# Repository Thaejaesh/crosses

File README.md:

# FORKED FROM ORIGINAL CREATOR: Good-Great-Grand-Wonderful @ https://github.com/Good-Great-Grand-Wonderful/crosses
# Crosses

A modular ergonomic columar staggered keyboard by Good Great Grand Wonderful LLC. 

Made with a precise trackball sensor. Eliminating the need to have another pointing device, everything is within reach.

Available at http://ergokeyboards.com

### Features

- Matrix with a thumb cluster that works better with our opposable thumbs!
- Main matrix layouts of: 3x5, 3x6, and 4x6
- Kailh Choc hotswap sockets, so you can explore and find your perfect switch
- Left/Right or dualing trackballs
- Optional OLED screens

### Firmware

QMK: https://github.com/Good-Great-Grand-Wonderful/qmk_firmware/tree/gggw/crosses

Vial: https://github.com/Good-Great-Grand-Wonderful/crosses-vial-qmk/tree/gggw/crosses

ZMK(testing): https://github.com/Good-Great-Grand-Wonderful/crosses-zmk

### Gerbers

Production ready and prepped with JLCPCB part numbers: [Gerbers](Gerbers)

### BOM

#### Cases

N = Number of trackballs

| Qty       |3x5 | 3x6 | 4x6 | Item                                              | Notes                             |
|-----------|----|-----|-----|---------------------------------------------------|-----------------------------------|
| 24        | x  | x   | x   | 3mm Heat set inserts                              |                                   |
| 16        | x  | x   | x   | 3mm x 5mm Hex Bolts                               | +2 for every trackball you delete |
| 2xN       | x  | x   | x   | 3mm x 12mm Hex Bolts                              |                                   |
| 2xN       | x  | x   | x   | 3mm x 8mm Hex Bolts                               |                                   |
| 1         | x  | x   | x   | Thumb Cluster PCB Panel                           |                                   |
| 4         | x  | x   | x   | Hirose FH12-14S 0.5SH 1x14 1MP P0.50mm Horizontal |                                   |
| 2         | x  | x   | x   | SM06B-SRSS-TB(LF)(SN)                             |                                   |
| 1         | x  |     |     | 3x5 Matrix PCB Panel                              |                                   |
| 1         |    | x   |     | 3x6 Matrix PCB Panel                              |                                   |
| 1         |    |     | x   | 4x6 Matrix PCB Panel                              |                                   |
| 2         | x  |     |     | 100mm 14p 0.5mm pitch FFC cables                  |                                   |
| 2         |    | x   | x   | 150mm 14p 0.5mm pitch FFC cables                  |                                   |
| 1xN       | x  | x   | x   | 100mm 6p JST SH 1.0 Same direction cables         |                                   |
| 2x        | x  | x   | x   | Thumb Cluster Case (one should be flipped)        |                                   |
| 2x        | x  |     |     | 3x5 Matrix Case    (one should be flipped)        |                                   |
| 2x        |    | x   |     | 3x6 Matrix Case    (one should be flipped)        |                                   |
| 2x        |    |     | x   | 4x6 Matrix Case    (one should be flipped)        |                                   |
| 36x       | x  |     |     | Kailh Choc Hotswap Sockets                        |                                   |
| 42x       |    | x   |     | Kailh Choc Hotswap Sockets                        |                                   |
| 54x       |    |     | x   | Kailh Choc Hotswap Sockets                        |                                   |
| 36x       | x  |     |     | 1N4148 SMD SOD-123 Resistors                      |                                   |
| 42x       |    | x   |     | 1N4148 SMD SOD-123 Resistors                      |                                   |
| 54x       |    |     | x   | 1N4148 SMD SOD-123 Resistors                      |                                   |
| 1xN       | x  | x   | x   | Trackball Mount    (one should be flipped)        |                                   |
| 1xN       | x  | x   | x   | Trackball PCB                                     | [Repo](https://github.com/Good-Great-Grand-Wonderful/PMW3360DM-T2QU)                                  |
| 1xN       | x  | x   | x   | PMW3360DM-T2QU + LM19-LSI                         | or sub a PMW3389                  |
| 1xN       | x  | x   | x   | Trackball Carrier Base                            |                                   |
| 1xN       | x  | x   | x   | Trackball Carrier Top                             |                                   |

## License

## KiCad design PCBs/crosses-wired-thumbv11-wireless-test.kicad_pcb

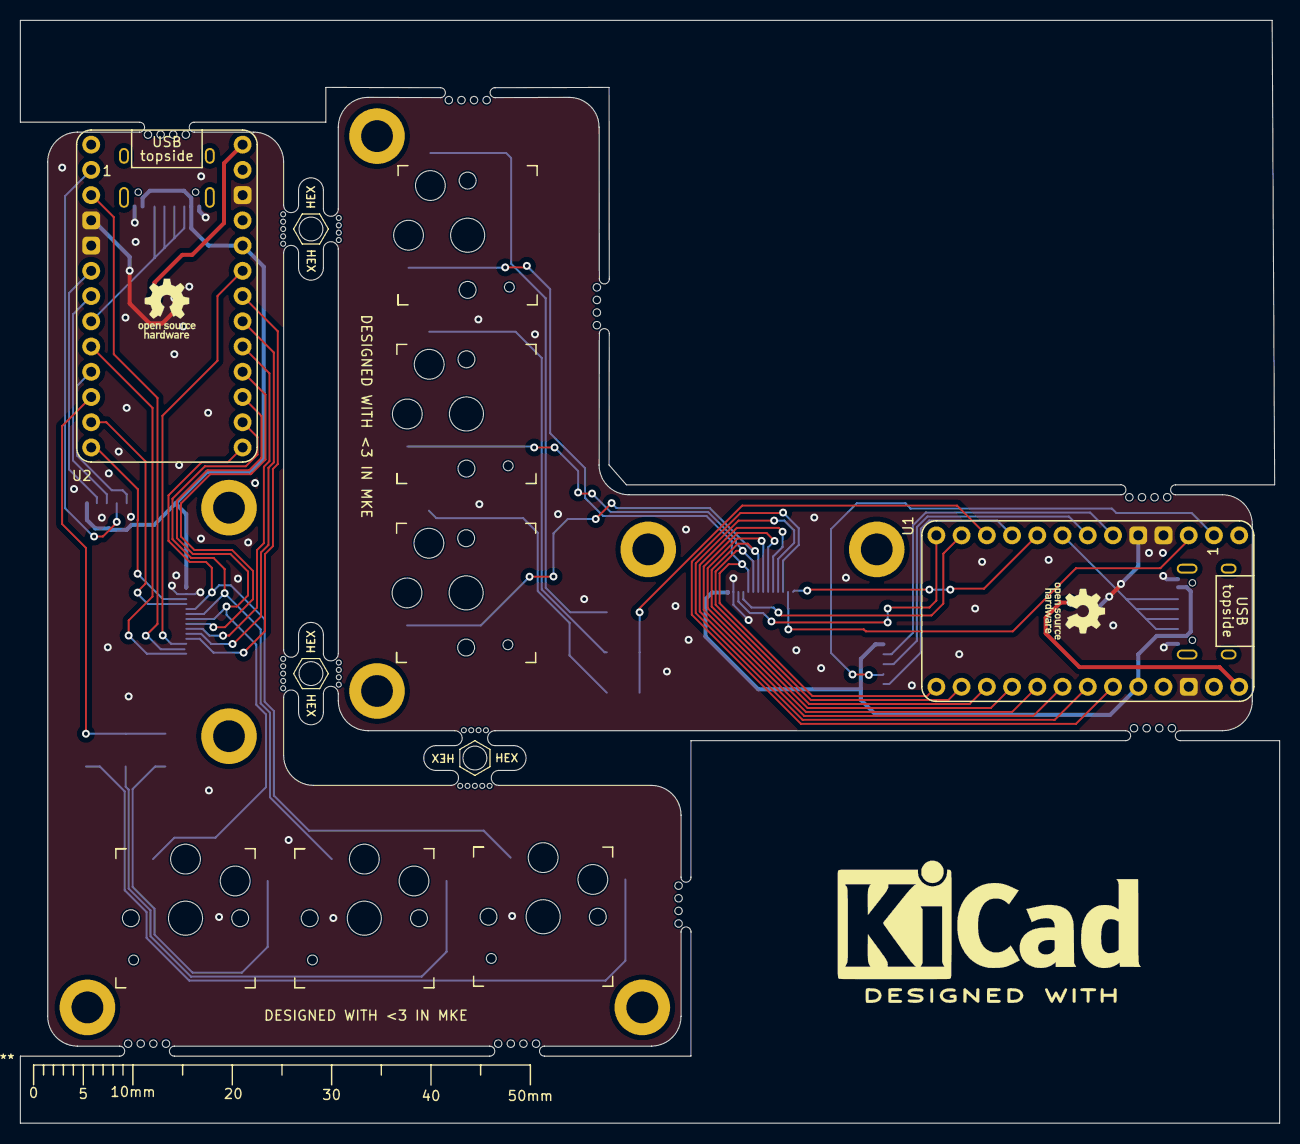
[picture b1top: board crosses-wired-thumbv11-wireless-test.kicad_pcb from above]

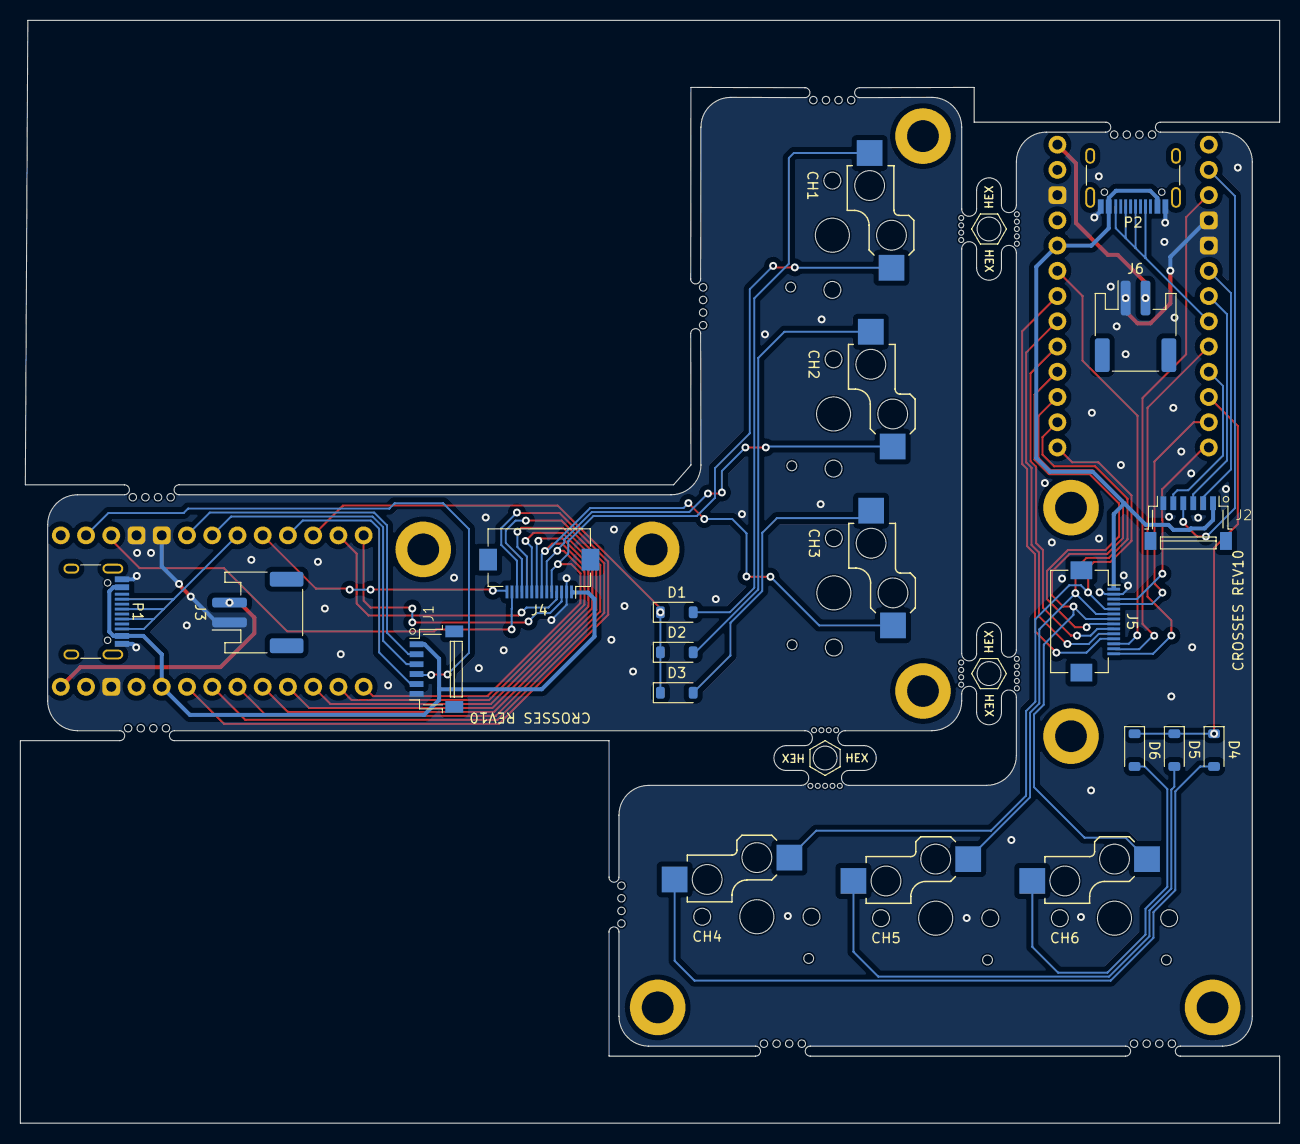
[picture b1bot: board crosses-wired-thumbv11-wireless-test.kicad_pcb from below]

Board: 2 copper layers, 126.8 x 111.0 mm, 33 parts (18 on the bottom side), 47 nets.

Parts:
CH1, CH2, CH3, CH4, CH5, CH6: CPG135001S30; Kailh_socket_PG1350
D1, D2, D3, D4, D5, D6: 1N4148; D_SOD-123
H1, H1#2, H2, H2#2, H3, H3#2, H3#3, H3#4: MountingHole; MountingHole_3.2mm_M3_DIN965_Pad
J1, J2: SM06B-SRSS-TB(LF)(SN)
J3, J6: Conn_01x02_Socket; JST_PH_S2B-PH-SM4-TB_1x02-1MP_P2.00mm_Horizontal
J4, J5: Conn_01x14_Pin; Hirose_FH12-14S-0.5SH_1x14-1MP_P0.50mm_Horizontal
MB5, MB5#2, MB5#3: 5.5mm; mousebites_5p5mm_easysnap
P1, P2: TYPE-C-31-M-12 USB; USB_C_Receptacle_HRO_TYPE-C-31-M-12
U1, U2: supermini nrf / nice nano v2; Helios_AH_USBup

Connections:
GND: J1.6, J2.6, J3.1, J4.2, J5.2, J6.1, P1.A1 (GND), P1.A12 (GND), P1.B1 (GND), P1.B12 (GND), P2.A1 (GND), P2.A12 (GND), P2.B1 (GND), P2.B12 (GND), U1.3 (GND), U1.4 (GND), U1.14 (GND), U2.3 (GND), U2.4 (GND), U2.14 (GND)
L-COL0: J4.9, U1.20 (F7)
L-COL1: J4.8, U1.21 (B1)
L-COL2: CH1.1, J4.5, U1.24 (B6)
L-COL3: CH2.1, J4.6, U1.23 (B2)
L-COL4: CH3.1, J4.7, U1.22 (B3)
L-COLP: J4.13, U1.2 (D2-RX)
L-CS: J1.5, U1.9 (D7)
L-DATA: P1.A5 (CC1), P1.A6 (D+), P1.B5 (CC2), P1.B6 (D+), U1.7 (D4)
L-I2C SCL: J4.3, U1.12 (B5)
L-I2C SDA: J4.4, U1.11 (B4)
L-MISO: J1.4, U1.1 (D3-TX)
L-MOSI: J1.3, U1.6 (D0)
L-ROW0: J4.10, U1.19 (F6)
L-ROW1: J4.11, U1.18 (F5)
L-ROW2: J4.12, U1.17 (F4)
L-ROW3: D1.1 (K), D2.1 (K), D3.1 (K), U1.10 (E6)
L-ROWH: J4.14, U1.8 (C6)
L-SCK: J1.2, U1.5 (D1)
L-VCC: J1.1, J4.1, P1.A4 (VBUS), P1.A9 (VBUS), P1.B4 (VBUS), P1.B9 (VBUS), U1.16 (VCC)
unnamed: CH1.2, D1.2 (A)
unnamed: CH2.2, D2.2 (A)
unnamed: CH3.2, D3.2 (A)
unnamed: CH4.2, D4.2 (A)
unnamed: CH5.2, D5.2 (A)
unnamed: CH6.2, D6.2 (A)
R-COL0: J5.9, U2.20 (F7)
R-COL1: J5.8, U2.21 (B1)
R-COL2: CH4.1, J5.5, U2.24 (B6)
R-COL3: CH5.1, J5.6, U2.23 (B2)
R-COL4: CH6.1, J5.7, U2.22 (B3)
R-COLP: J5.13, U2.2 (D2-RX)
R-CS: J2.5, U2.9 (D7)
R-DATA: P2.A5 (CC1), P2.A6 (D+), P2.B5 (CC2), P2.B6 (D+), U2.7 (D4)
R-I2C SCL: J5.3, U2.12 (B5)
R-I2C SDA: J5.4, U2.11 (B4)
R-MISO: J2.4, U2.1 (D3-TX)
R-MOSI: J2.3, U2.6 (D0)
R-ROW0: J5.10, U2.19 (F6)
R-ROW1: J5.11, U2.18 (F5)
R-ROW2: J5.12, U2.17 (F4)
R-ROW3: D4.1 (K), D5.1 (K), D6.1 (K), U2.10 (E6)
R-ROWH: J5.14, U2.8 (C6)
R-SCK: J2.2, U2.5 (D1)
R-VCC: J2.1, J5.1, P2.A4 (VBUS), P2.A9 (VBUS), P2.B4 (VBUS), P2.B9 (VBUS), U2.16 (VCC)
VBATTL: J3.2, U1.30 (VBUS)
VBATTR: J6.2, U2.30 (VBUS)

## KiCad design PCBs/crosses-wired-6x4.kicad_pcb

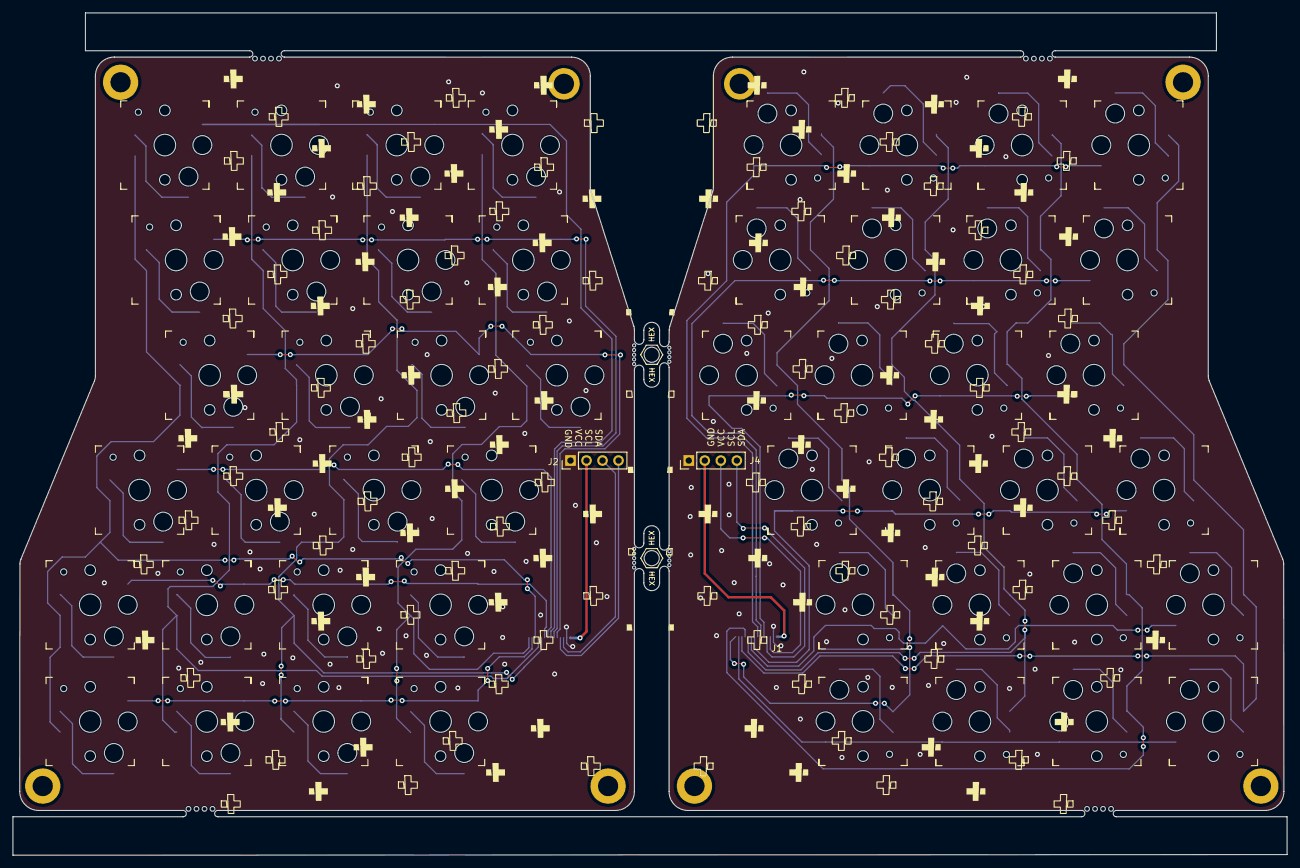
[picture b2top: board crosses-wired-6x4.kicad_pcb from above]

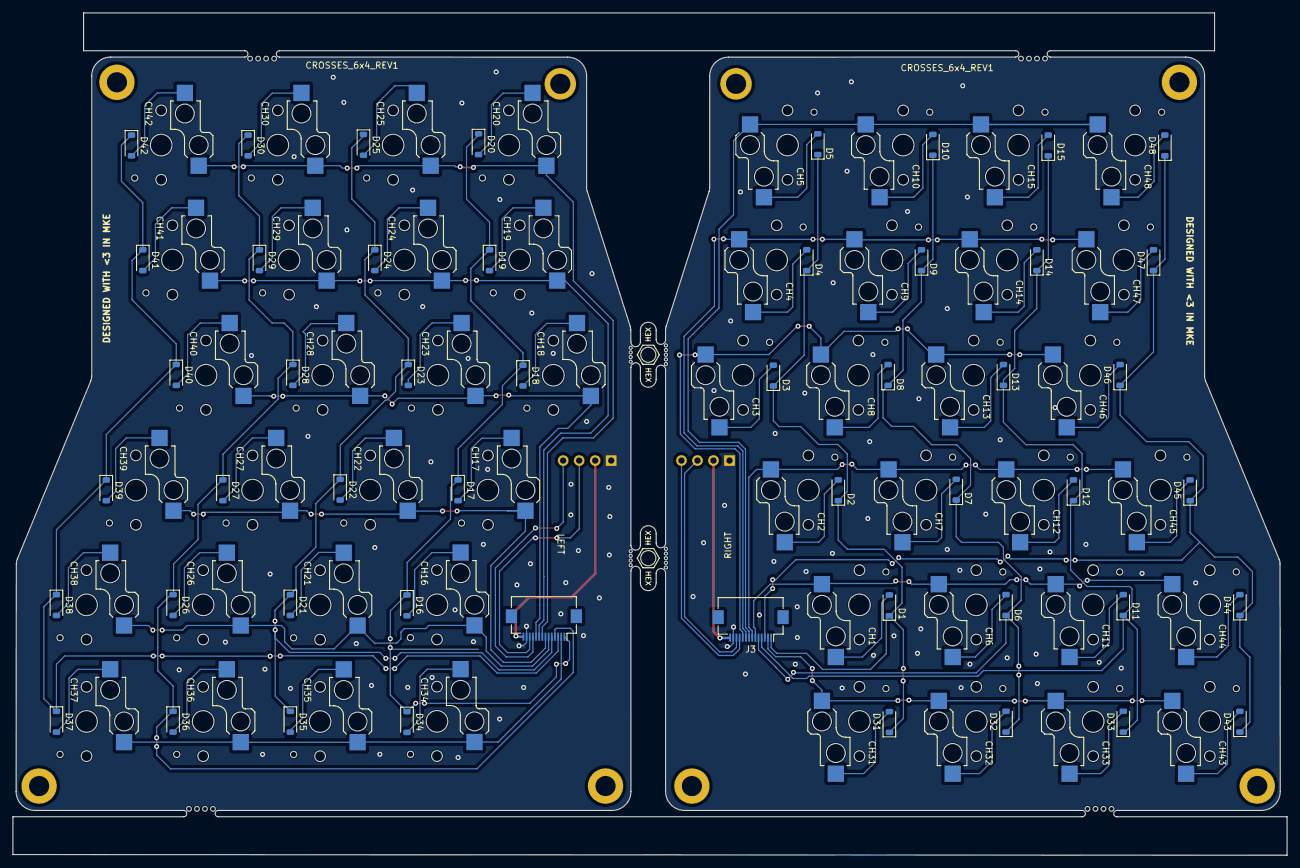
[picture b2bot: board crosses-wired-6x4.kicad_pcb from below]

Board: 2 copper layers, 202.1 x 133.6 mm, 110 parts (54 on the bottom side), 75 nets.

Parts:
CH1, CH2, CH3, CH4, CH5, CH6, CH7, CH8, CH9, CH10, CH11, CH12, CH13, CH14, CH15, CH16, CH17, CH18, CH19, CH20, CH21, CH22, CH23, CH24, CH25, CH26, CH27, CH28, CH29, CH30, CH31, CH32, CH33, CH34, CH35, CH36, CH37, CH38, CH39, CH40, CH41, CH42, CH43, CH44, CH45, CH46, CH47, CH48: CPG135001S30; Kailh_socket_PG1350
D1, D2, D3, D4, D5, D6, D7, D8, D9, D10, D11, D12, D13, D14, D15, D16, D17, D18, D19, D20, D21, D22, D23, D24, D25, D26, D27, D28, D29, D30, D31, D32, D33, D34, D35, D36, D37, D38, D39, D40, D41, D42, D43, D44, D45, D46, D47, D48: 1N4148; D_SOD-123
H1, H1#2, H3, H3#2, H5, H5#2, H6, H6#2: MountingHole; MountingHole_3.2mm_M3_DIN965_Pad
J1, J3: Conn_01x14_Pin; Hirose_FH12-14S-0.5SH_1x14-1MP_P0.50mm_Horizontal
J2, J4: Conn_01x04_Socket; PinHeader_1x04_P2.54mm_Vertical
MB5, MB5#2: 5.5mm; mousebites_5p5mm_easysnap

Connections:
GND: J1.13, J2.1, J3.13, J4.1
L-COL0: CH1.1, CH6.1, CH11.1, CH44.1, J3.6
L-COL1: CH2.1, CH7.1, CH12.1, CH45.1, J3.7
L-COL2: CH3.1, CH8.1, CH13.1, CH46.1, J3.10
L-COL3: CH4.1, CH9.1, CH14.1, CH47.1, J3.9
L-COL4: CH5.1, CH10.1, CH15.1, CH48.1, J3.8
L-COLP: CH31.1, CH32.1, CH33.1, CH43.1, J3.2
L-ROW0: D6.1 (K), D7.1 (K), D8.1 (K), D9.1 (K), D10.1 (K), D32.1 (K), J3.5
L-ROW1: D11.1 (K), D12.1 (K), D13.1 (K), D14.1 (K), D15.1 (K), D33.1 (K), J3.4
L-ROW2: D43.1 (K), D44.1 (K), D45.1 (K), D46.1 (K), D47.1 (K), D48.1 (K), J3.3
L-ROW-N1: D1.1 (K), D2.1 (K), D3.1 (K), D4.1 (K), D5.1 (K), D31.1 (K), J3.1
unnamed: CH1.2, D1.2 (A)
unnamed: CH2.2, D2.2 (A)
unnamed: CH3.2, D3.2 (A)
unnamed: CH4.2, D4.2 (A)
unnamed: CH5.2, D5.2 (A)
unnamed: CH6.2, D6.2 (A)
unnamed: CH7.2, D7.2 (A)
unnamed: CH8.2, D8.2 (A)
unnamed: CH9.2, D9.2 (A)
unnamed: CH10.2, D10.2 (A)
unnamed: CH11.2, D11.2 (A)
unnamed: CH12.2, D12.2 (A)
unnamed: CH13.2, D13.2 (A)
unnamed: CH14.2, D14.2 (A)
unnamed: CH15.2, D15.2 (A)
unnamed: CH16.2, D16.2 (A)
unnamed: CH17.2, D17.2 (A)
unnamed: CH18.2, D18.2 (A)
unnamed: CH19.2, D19.2 (A)
unnamed: CH20.2, D20.2 (A)
unnamed: CH21.2, D21.2 (A)
unnamed: CH22.2, D22.2 (A)
unnamed: CH23.2, D23.2 (A)
unnamed: CH24.2, D24.2 (A)
unnamed: CH25.2, D25.2 (A)
unnamed: CH26.2, D26.2 (A)
unnamed: CH27.2, D27.2 (A)
unnamed: CH28.2, D28.2 (A)
unnamed: CH29.2, D29.2 (A)
unnamed: CH30.2, D30.2 (A)
unnamed: CH31.2, D31.2 (A)
unnamed: CH32.2, D32.2 (A)
unnamed: CH33.2, D33.2 (A)
unnamed: CH34.2, D34.2 (A)
unnamed: CH35.2, D35.2 (A)
unnamed: CH36.2, D36.2 (A)
unnamed: CH37.2, D37.2 (A)
unnamed: CH38.2, D38.2 (A)
unnamed: CH39.2, D39.2 (A)
unnamed: CH40.2, D40.2 (A)
unnamed: CH41.2, D41.2 (A)
unnamed: CH42.2, D42.2 (A)
unnamed: CH43.2, D43.2 (A)
unnamed: CH44.2, D44.2 (A)
unnamed: CH45.2, D45.2 (A)
unnamed: CH46.2, D46.2 (A)
unnamed: CH47.2, D47.2 (A)
unnamed: CH48.2, D48.2 (A)
R-COL0: CH16.1, CH21.1, CH26.1, CH38.1, J1.6
R-COL1: CH17.1, CH22.1, CH27.1, CH39.1, J1.7
R-COL2: CH18.1, CH23.1, CH28.1, CH40.1, J1.10
R-COL3: CH19.1, CH24.1, CH29.1, CH41.1, J1.9
R-COL4: CH20.1, CH25.1, CH30.1, CH42.1, J1.8
R-COLP: CH34.1, CH35.1, CH36.1, CH37.1, J1.2
R-ROW0: D21.1 (K), D22.1 (K), D23.1 (K), D24.1 (K), D25.1 (K), D35.1 (K), J1.5
R-ROW1: D26.1 (K), D27.1 (K), D28.1 (K), D29.1 (K), D30.1 (K), D36.1 (K), J1.4
R-ROW2: D37.1 (K), D38.1 (K), D39.1 (K), D40.1 (K), D41.1 (K), D42.1 (K), J1.3
R-ROW-N1: D16.1 (K), D17.1 (K), D18.1 (K), D19.1 (K), D20.1 (K), D34.1 (K), J1.1
SCL: J2.3, J3.12
SCL-R: J1.12, J4.3
SDA: J2.4, J3.11
SDA-R: J1.11, J4.4
VCC: J2.2, J3.14
VCC-R: J1.14, J4.2

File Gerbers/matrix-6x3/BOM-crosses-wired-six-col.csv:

Comment,Designator,Footprint,LCSC,Quantity
Conn_01x14_Pin,"J1,J3",Hirose_FH12-14S-0.5SH_1x14-1MP_P0.50mm_Horizontal,C5378715,2
1N4148,"D1,D10,D11,D12,D13,D14,D15,D16,D17,D18,D19,D2,D20,D21,D22,D23,D24,D25,D26,D27,D28,D29,D3,D30,D31,D32,D33,D34,D35,D36,D4,D5,D6,D7,D8,D9",D_SOD-123,C81598,36
MountingHole,H3,MountingHole_3.2mm_M3_DIN965_Pad,,1
MountingHole,H1,MountingHole_3.2mm_M3_DIN965_Pad,,1
MountingHole,H6,MountingHole_3.2mm_M3_DIN965_Pad,,1
MountingHole,H5,MountingHole_3.2mm_M3_DIN965_Pad,,1

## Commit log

2024-12-28 [CHORE] Adding models
2024-12-28 [MINOR] Adding trackball mount
2025-01-03 Add 4x6, add new version of thumb cluster
2025-01-09 Adding PCBs
2025-01-09 Add OSH logos
2025-01-10 Adding test wireless PCB
2025-01-10 Adding licenses
2025-01-10 Update LICENSE_CC
2025-01-10 CC-BY-NC
2025-01-10 I am way too sick for this
2025-01-14 Updating case designs
2025-01-15 Updating models
2025-02-08 Adding Bridges models
2025-02-10 Adding production gerbers
2025-02-14 Updating 4x6
2025-02-19 [MINOR] Add variant indicators to cases
2025-06-09 Update README.md
    Added reference to original creator and repo

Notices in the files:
README.md:
License:
CC BY-NC 4.0
